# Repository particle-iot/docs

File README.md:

Particle Documentation 
======================

Here you'll find the documentation for the Particle platform, including
the Particle Device Cloud, Photon, Electron, and Spark Core.

To view this documentation, visit [our website](https://docs.particle.io), where the documentation is hosted.

Local Hosting
-------------

This documentation uses a fabulous tool from the folks at Segment called [Metalsmith](http://www.metalsmith.io). Metalsmith is a static site generator that builds static HTML sites from source material in other formats; in this case, Markdown and Handlebars.

To set up a server running at `http://localhost:8080`, follow the installation instructions below...

> _**NOTE:** Any changes made to the source content should be automatically picked up by the browser via `livereload`._

### Bare-metal Hosting

#### Device Setup

To host this documentation locally, you'll need Node.js and npm (see the `engines` section of `package.json` for the exact versions):

If you don't have node.js installed, you can download the installer (LTS recommended) from [nodejs.org](https://nodejs.org/en/).

Once you have Node.js set up, navigate to the `docs` directory on your machine, and use the following commands:

#### Install Dependencies

To install any other necessary dependencies, run:

```none
npm install
```

#### Spell checking

To check the spelling of all Markdown files, run:

```none
npm run spell
```

This is a good idea when you edit any .md files because it not only checks regular spelling, but it will flag if you don't capitalize and spell things exactly like the rest of the docs. For example: U.FL, Wi-Fi, etc..

Actually, these two files are currently skipped because something in the files confuse the spelling checker and cause it to lose track of word breaks and then things fail horribly:

- src/content/reference/asset-tracking/tracker-edge-firmware.md
- src/content/reference/device-os/firmware.md

#### Testing

If you are making non-trivial changes, it’s a good idea to check links using the crawler. This takes a number of minutes to run:

```none
npm test
```

If errors are reported, fix them and run the test again. The second time it will be much faster because it will have cached many of the lookups.

Link checking is not done on commits or pull requests due to the variable amount of time it takes and that it may randomly fail, making it hard to publish at a specific time.

#### Running locally

```none
npm start
```

Once the output stops, 

#### Generate PDF datasheets

```none
npm run pdf-generation
```

### Containerized Hosting

If you have Docker installed, then you can simply run the following commands to get started...

```none
$ cd <particle-iot/docs>/
$ scripts/docker-server.sh --help

usage: particle-docs [--build] [--deploy] [--run-tests] [--spell-check]

Build, test and deploy a local documentation server.

  -b, --build           Build and install documentation packages.
  -d, --deploy          Launch documentation server at https://localhost:8080.
  -h, --help            Display this help and exit.
  -s, --spell-check     Run the spell-checker to verify spelling and update dictionary file.
  -t, --run-tests       Run CI tests.

NOTE: If no options are specified, then ALL options will be selected.
```

> _**NOTE:** Containerized hosting is currently only available on Linux devices. Mac is has an [open issue](https://github.com/docker/for-mac/issues/2965) involving `localhost`, and Windows has not been tested at this time._

The containerized version is not regularly used. It will probably work, but is not guaranteed to.

Command line tools
------------------

The `scripts` directory contains a number of maintenance tools. They all share the dependencies in the top-level `package.json`, so a single `npm install` in the top of the repository is all that's needed. Run them from the top of the repository using `npm run`. To pass options to a tool, put them after `--`:

```none
npm run library-tool -- --generate
```

| Command | Description |
| :--- | :--- |
| `npm run api-rename-section` | Rename a section of the Device OS API reference (interactive) |
| `npm run carriers-update` | Update docs Markdown when `carriers.json` is updated |
| `npm run export-md` | Export a docs page to Markdown (`--dest` is relative to the top of the repository) |
| `npm run fake-data` | Generate fake data (device IDs, serial numbers, ICCIDs) for testing |
| `npm run fix-links` | Fix links within the docs |
| `npm run fix-tracker-hex` | Fix hex files for the Tracker device |
| `npm run library-tool` | Particle library tester and data generating tool (see below) |
| `npm run map-fix` | Update the world map SVG |
| `npm run menu-json-upgrade` | Upgrade menu JSON files |
| `npm run move-page` | Move a docs page and add redirects (interactive) |
| `npm run pin-info-update` | Fix up the `pinInfo.json` file |
| `npm run pinmap-diagram` | Generate pinmap diagram SVG files |
| `npm run power-consumption` | Parse the power consumption reference manual (put the HTML export in `scripts/power-consumption/power.html`) |
| `npm run release-update` | Update release notes and device restore binaries for new Device OS releases |
| `npm run ticket-forms` | Extract ticket forms and fields from the Zendesk guide (requires the `ZENDESK_AUTH` environment variable) |
| `npm run title-case-fixer` | Fix capitalization of Markdown headers |
| `npm run update-app-notes` | Update the application notes tiles from the marketing website (requires Node.js 20 or later) |

The `scripts/ticket-processor` tool runs on a different server, so it is not part of the top-level package. It has its own `package.json` and is run from its own directory using `npm install` and `node app.js`.

### Access token

The `library-tool` and `release-update` tools need a Particle API access token. Copy `scripts/config.example.json` to `scripts/config.json` (which is not committed to git) and edit it:

```json
{
    "accessToken": "xxx"
}
```

Shared code for reading this file is in `scripts/lib/script-config.js`.

### Library tool

```none
npm run library-tool -- --fetch-library-list --download-libraries --test-builds --generate
```

Options:

- `--fetch-library-list` Downloads the library list from the API instead of using `data/libraryList.json`
- `--download-libraries` Downloads any missing libraries to `data/libraries`
- `--test-builds` Tests any libraries that have not been built. Build status is stored in `data/libraryData.json`
- `--generate` Generates data files in the docs repository (this also does `--generate-index`)
- `--generate-index` Generates an abbreviated index of libraries in `src/assets/files/libraryIndex.json`

These are in the `scripts/LibraryTool` directory. Note that `data/libraries` and `data/libraryList.json` are not committed to github, as they are huge and can be regenerated if needed. The build status in `data/libraryData.json` is stored.

Updating Production Documentation
---------------------------------

When updated documentation is pushed to the `master` branch, it is automatically pushed to Amazon S3 by Circle CI.

Organization
------------

The majority of the content herein is stored in the `src/content` directory as a set of Markdown files. Assets such as images and javascript are stored in the `src/assets` directory.

### Structuring your content

The docs dynamically generate a table of contents for navigation purposes based on the headers (i.e. `###`) that you use on each page. It is important to note that _order and hierarchy matters_ when you are designing the organization of content on your page. Your page should include the following:

* 1 `h1` at the top of the page that will serve as the title of the page. You can even copy the `title` directly from the front-matter of the markdown file like this: `# {{title}}`

* As many `h2`s (`##`) as you'd like to serve as the section headers for the page.

* Underneath every `h2`, if applicable, as many `h3`s (`###`) as you'd like to serve as sub-sections within the section. These will appear as nested within the navigation on the left.

Note that there are only 2 levels of navigation that will appear in the table of contents. *`h4`s and below will not appear in the table of contents*.

### Redirects

When moving pages around or defining the default page for a section, add redirect links to [`redirects.json`](config/redirects.json).

Attributions
------------

Some of this documentation is derived from the [Arduino documentation](http://arduino.cc/en/Reference), as the Arduino/Wiring language and libraries are used extensively on the Spark Core.

This documentation was originally built using [Flatdoc](http://ricostacruz.com/flatdoc/), an awesome tool for building beautiful documentation from simple Markdown files. We have made many modifications since, but the inspiration remains.

Contributions
-------------

This documentation is managed by Particle, but supported by the community. We welcome contributions such as:

* Edits to improve grammar or fix typos (run `npm run spell` for automated spell check)
* Edits to improve clarity
* Additional annotated examples for others to follow
* Additional content that would help provide a complete understanding of the Particle platform
* Translations to other languages

Making a contribution is as simple as forking this repository, making edits to your fork, and contributing those edits as a pull request. For more information on how to make a pull request, see [GitHub's documentation](https://help.github.com/articles/using-pull-requests/).

License
-------

These files have been made available online through a [Creative Commons Attribution-ShareAlike 3.0 license](http://creativecommons.org/licenses/by-sa/3.0/us/).

You are welcome to distribute, remix, and use these files for commercial purposes. If you do so, please attribute the original design to Particle both on the website and on the physical packaging of the product or in the instruction manual. All derivative works must be published under the same or a similar license.

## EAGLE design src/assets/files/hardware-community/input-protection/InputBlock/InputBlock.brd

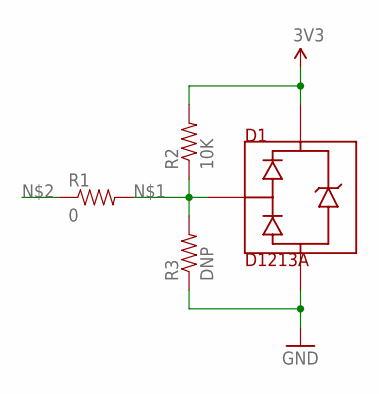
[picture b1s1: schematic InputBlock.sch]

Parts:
D1: D1213A; DLP
R1: 0; 0603-RES
R2: 10K; 0603-RES
R3: DNP; 0603-RES

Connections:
3V3: D1.VCC, R2.2
GND: D1.GND, R3.1
unnamed: D1.SIGNAL, R1.2, R2.1, R3.2

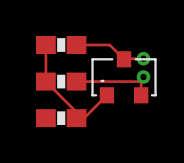
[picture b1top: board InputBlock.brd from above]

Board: 2 copper layers, 4 parts (0 on the bottom side), 3 nets.

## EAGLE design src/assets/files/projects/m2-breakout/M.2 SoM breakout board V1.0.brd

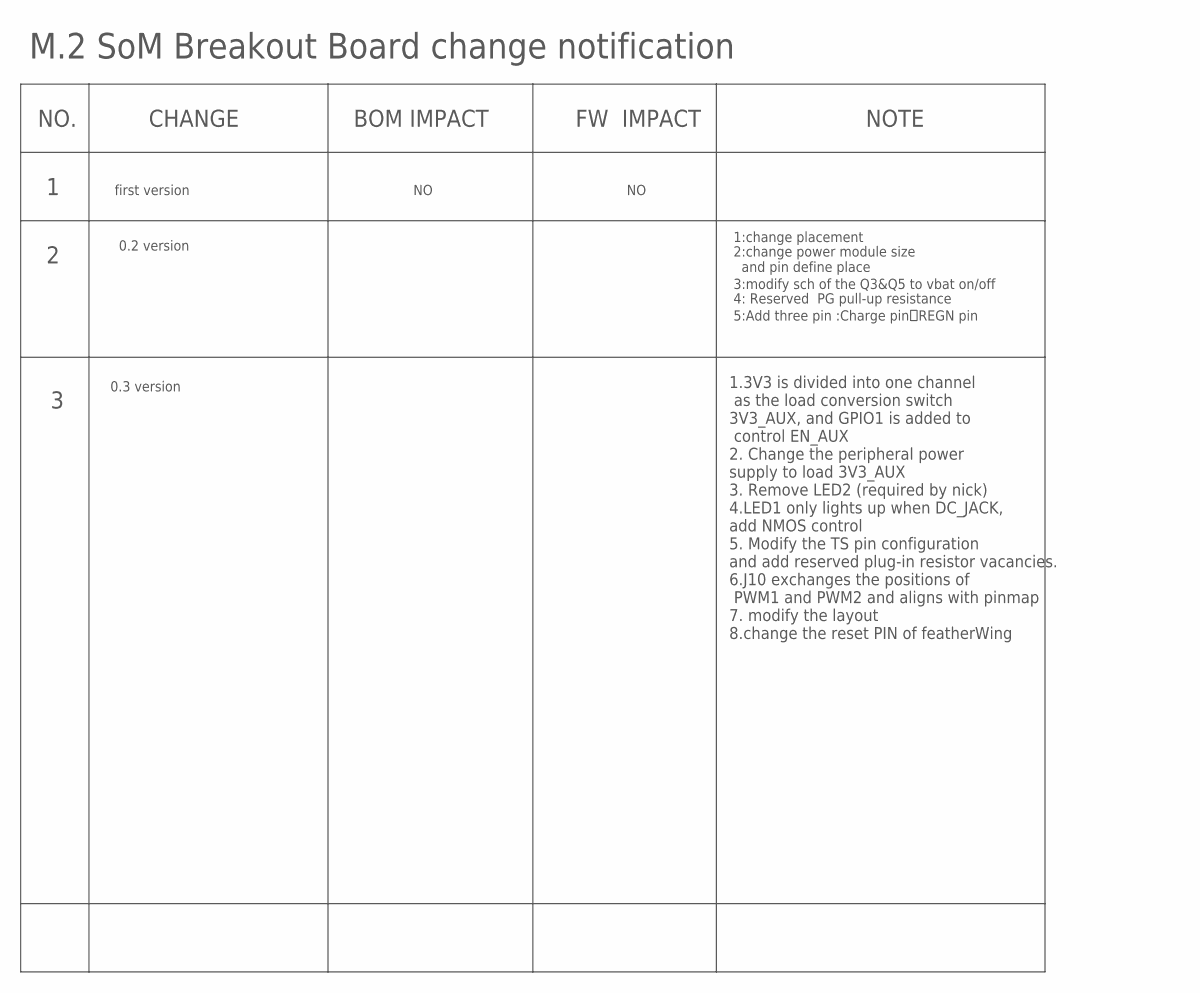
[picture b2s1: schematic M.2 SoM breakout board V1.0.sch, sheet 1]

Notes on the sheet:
NO.
CHANGE
BOM IMPACT
FW IMPACT
NOTE
first version
M.2 SoM Breakout Board change notification
0.2 version
1:change placement
3:modify sch of the Q3&Q5 to vbat on/off
5:Add three pin :Charge pin，REGN pin
2:change power module size and pin define place
4: Reserved PG pull-up resistance
0.3 version
1.3V3 is divided into one channel as the load conversion switch 3V3_AUX, and GPIO1 is added to control EN_AUX 2. Change the peripheral power supply to load 3V3_AUX 3. Remove LED2 (required by nick) 4.LED1 only lights up when DC_JACK, add NMOS control 5. Modify the TS pin configuration and add reser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

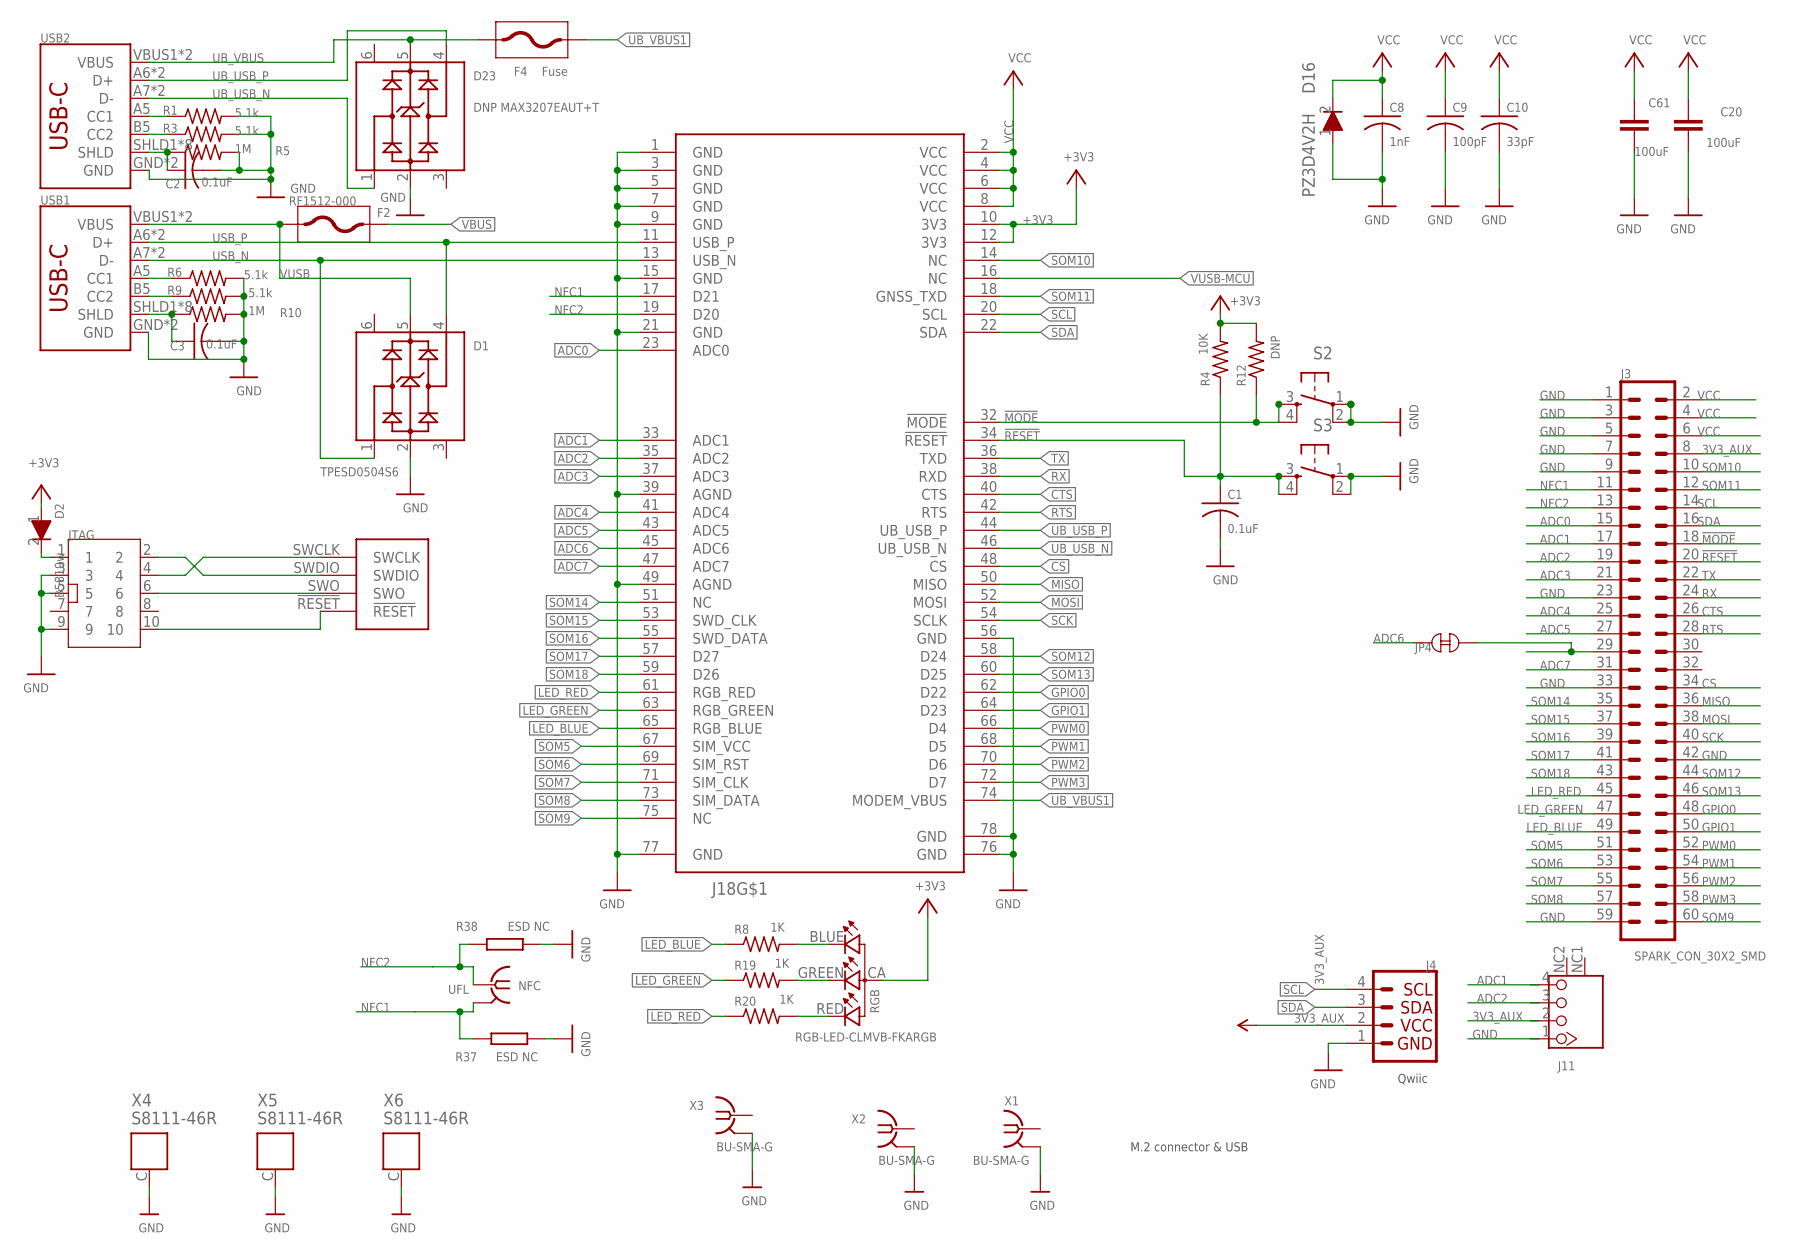
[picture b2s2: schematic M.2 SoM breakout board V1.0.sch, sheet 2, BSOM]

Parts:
C1, C2, C3: 0.1uF; C0402_B
C8: 1nF; C0402_B
C9: 100pF; C0402_B
C10: 33pF; C0402_B
C20, C61: 100uF; C1206K
D1: TPESD0504S6; SOT23-6
D2: B5819w; SOD-123
D16: PZ3D4V2H; SOD-323
D23: DNP MAX3207EAUT+T; SOT23-6
F2: RF1512-000; F0805
F4: Fuse; F0805
J3: SPARK_CON_30X2_SMD
J4: QWIIC_CONNECTORJS-1MM; 1X04_1MM_RA
J11: WAFER-HY2.0-4PWB; M.2-SOM-BREAKOUT-BOARD-V0.2-0228_WAFER-HY2.0-4PWB
J18: PARTICLE-STUDIOS_M_SERIES_M.2KEY; PARTICLE-STUDIOS_PARTICLE_M.2EKEY_3.65MM_DRILL
JP4: TP_SHORT
JTAG: CONN5X2; CONN5X2_1.27; MPN P6014A-M2GC-030-10
NFC: UFL; IPEX-20279-001E
R1, R3, R6, R9: 5.1k; R0402_B
R4: 10K; R0402_B
R5, R10: 1M; R0402_B
R8, R19, R20: 1K; R0402_B
R12: DNP; R0402_B
R37, R38: ESD NC; R-0402S
RGB: RGB-LED-CLMVB-FKARGB; PLCC4-2MM-RGB
S2, S3: TAC_SWITCH; TACTILE_SWITCH_4.2*3.2
USB1, USB2: USB_C16PIN; USB-C-16P
X1, X2, X3: BU-SMA-G
X4, X5, X6: S8111-46R

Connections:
3V3_AUX: J3.8, J4.2, J11.2; also elsewhere on the board
!MODE: J3.18, J18.32 (!MODE), R12.1, S2.3, S2.4
!RESET: C1.1, J3.20, J18.34 (!RESET), J18.!RESET, JTAG.10, R4.1, S3.3, S3.4; also elsewhere on the board
+3V3: D2.1, J18.10 (3V3), J18.12 (3V3), R4.2, R12.2, RGB.CA (1); also elsewhere on the board
ADC0: J3.15, J18.23 (ADC0); also elsewhere on the board
ADC1: J3.17, J11.4, J18.33 (ADC1); also elsewhere on the board
ADC2: J3.19, J11.3, J18.35 (ADC2); also elsewhere on the board
ADC3: J3.21, J18.37 (ADC3); also elsewhere on the board
ADC4: J3.25, J18.41 (ADC4); also elsewhere on the board
ADC5: J3.27, J18.43 (ADC5); also elsewhere on the board
ADC6: J18.45 (ADC6), JP4.2; also elsewhere on the board
ADC7: J3.31, J18.47 (ADC7)
CS: J3.34, J18.48 (CS); also elsewhere on the board
CTS: J3.26, J18.40 (CTS); also elsewhere on the board
GND: C1.2, C2.2, C3.2, C8.2, C9.2, C10.2, C20.2, C61.2, D1.2, D16.1, D23.2, J3.1, J3.3, J3.5, J3.7, J3.9, J3.23, J3.33, J3.42, J3.59, J4.1, J11.1, J18.1 (GND), J18.3 (GND), J18.5 (GND), J18.7 (GND), J18.9 (GND), J18.15 (GND), J18.21 (GND), J18.39 (AGND), J18.49 (AGND), J18.56 (GND), J18.76 (GND), J18.77 (GND), J18.78 (GND), JTAG.3, JTAG.5, JTAG.9, R1.2, R3.2, R5.2, R6.2, R9.2, R10.2, R37.2, R38.1, S2.1, S2.2, S3.1, S3.2, USB1.GND, USB1.GND2 (GND), USB2.GND, USB2.GND2 (GND), X1.2, X1.3 (2), X1.4 (2), X1.5 (2), X2.2, X2.3 (2), X2.4 (2), X2.5 (2), X3.2, X3.3 (2), X3.4 (2), X3.5 (2), X4.C, X5.C, X6.C; also elsewhere on the board
GPIO0: J3.48, J18.62 (D22); also elsewhere on the board
GPIO1: J3.50, J18.64 (D23); also elsewhere on the board
LED_BLUE: J3.49, J18.65 (RGB_BLUE), R8.1
LED_BLUE1: R8.2, RGB.BLUE (2)
LED_GREEN: J3.47, J18.63 (RGB_GREEN), R19.1
LED_GREEN1: R19.2, RGB.GREEN (3)
LED_RED: J3.45, J18.61 (RGB_RED), R20.1
LED_RED1: R20.2, RGB.RED (4)
MISO: J3.36, J18.50 (MISO); also elsewhere on the board
MOSI: J3.38, J18.52 (MOSI); also elsewhere on the board
unnamed: R1.1, USB2.A5 (CC1)
unnamed: R3.1, USB2.B5 (CC2)
unnamed: C2.1, R5.1, USB2.SHLD1 (SHLD), USB2.SHLD2 (SHLD), USB2.SHLD3 (SHLD), USB2.SHLD4 (SHLD), USB2.SHLD5 (SHLD), USB2.SHLD6 (SHLD), USB2.SHLD7 (SHLD), USB2.SHLD8 (SHLD)
unnamed: R6.1, USB1.A5 (CC1)
unnamed: R9.1, USB1.B5 (CC2)
unnamed: D2.2, JTAG.1
unnamed: C3.1, R10.1, USB1.SHLD1 (SHLD), USB1.SHLD2 (SHLD), USB1.SHLD3 (SHLD), USB1.SHLD4 (SHLD), USB1.SHLD5 (SHLD), USB1.SHLD6 (SHLD), USB1.SHLD7 (SHLD), USB1.SHLD8 (SHLD)
unnamed: J3.29, JP4.1
NFC1: J3.11, J18.17 (D21), NFC.2@1 (GND), NFC.2@2 (GND), R37.1
NFC2: J3.13, J18.19 (D20), NFC.1, R38.2
PWM0: J3.52, J18.66 (D4); also elsewhere on the board
PWM1: J3.54, J18.68 (D5); also elsewhere on the board
PWM2: J3.56, J18.70 (D6); also elsewhere on the board
PWM3: J3.58, J18.72 (D7); also elsewhere on the board
RTS: J3.28, J18.42 (RTS)
RX: J3.24, J18.38 (RXD); also elsewhere on the board
SCK: J3.40, J18.54 (SCLK); also elsewhere on the board
SCL: J3.14, J4.4, J18.20 (SCL); also elsewhere on the board
SDA: J3.16, J4.3, J18.22 (SDA); also elsewhere on the board
SOM5: J3.51, J18.67 (SIM_VCC)
SOM6: J3.53, J18.69 (SIM_RST)
SOM7: J3.55, J18.71 (SIM_CLK)
SOM8: J3.57, J18.73 (SIM_DATA)
SOM9: J3.60, J18.75 (NC)
SOM10: J3.10, J18.14 (NC)
SOM11: J3.12, J18.18 (GNSS_TXD)
SOM12: J3.44, J18.58 (D24)
SOM13: J3.46, J18.60 (D25)
SOM14: J3.35, J18.51 (NC)
SOM15: J3.37, J18.53 (SWD_CLK)
SOM16: J3.39, J18.55 (SWD_DATA)
SOM17: J3.41, J18.57 (D27)
SOM18: J3.43, J18.59 (D26)
SWCLK: J18.SWCLK, JTAG.4
SWDIO: J18.SWDIO, JTAG.2
SWO: J18.SWO, JTAG.6
TX: J3.22, J18.36 (TXD); also elsewhere on the board
UB_USB_N: D23.1, J18.46 (UB_USB_N), USB2.A7 (D-), USB2.B7 (D-)
UB_USB_P: D23.4, J18.44 (UB_USB_P), USB2.A6 (D+), USB2.B6 (D+)
UB_VBUS: D23.5, F4.P$2 (2), USB2.VBUS1 (VBUS), USB2.VBUS2 (VBUS)
UB_VBUS1: F4.P$1 (1), J18.74 (MODEM_VBUS)
USB_N: D1.1, J18.13 (USB_N), USB1.A7 (D-), USB1.B7 (D-)
USB_P: D1.4, J18.11 (USB_P), USB1.A6 (D+), USB1.B6 (D+)
VBUS: F2.P$2 (2); also elsewhere on the board
VCC: C8.1, C9.1, C10.1, C20.1, C61.1, D16.2, J3.2, J3.4, J3.6, J18.2 (VCC), J18.4 (VCC), J18.6 (VCC), J18.8 (VCC); also elsewhere on the board
VUSB: D1.5, F2.P$1 (1), USB1.VBUS1 (VBUS), USB1.VBUS2 (VBUS)
VUSB-MCU: J18.16 (NC); also elsewhere on the board

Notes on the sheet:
Qwiic
M.2 connector & USB

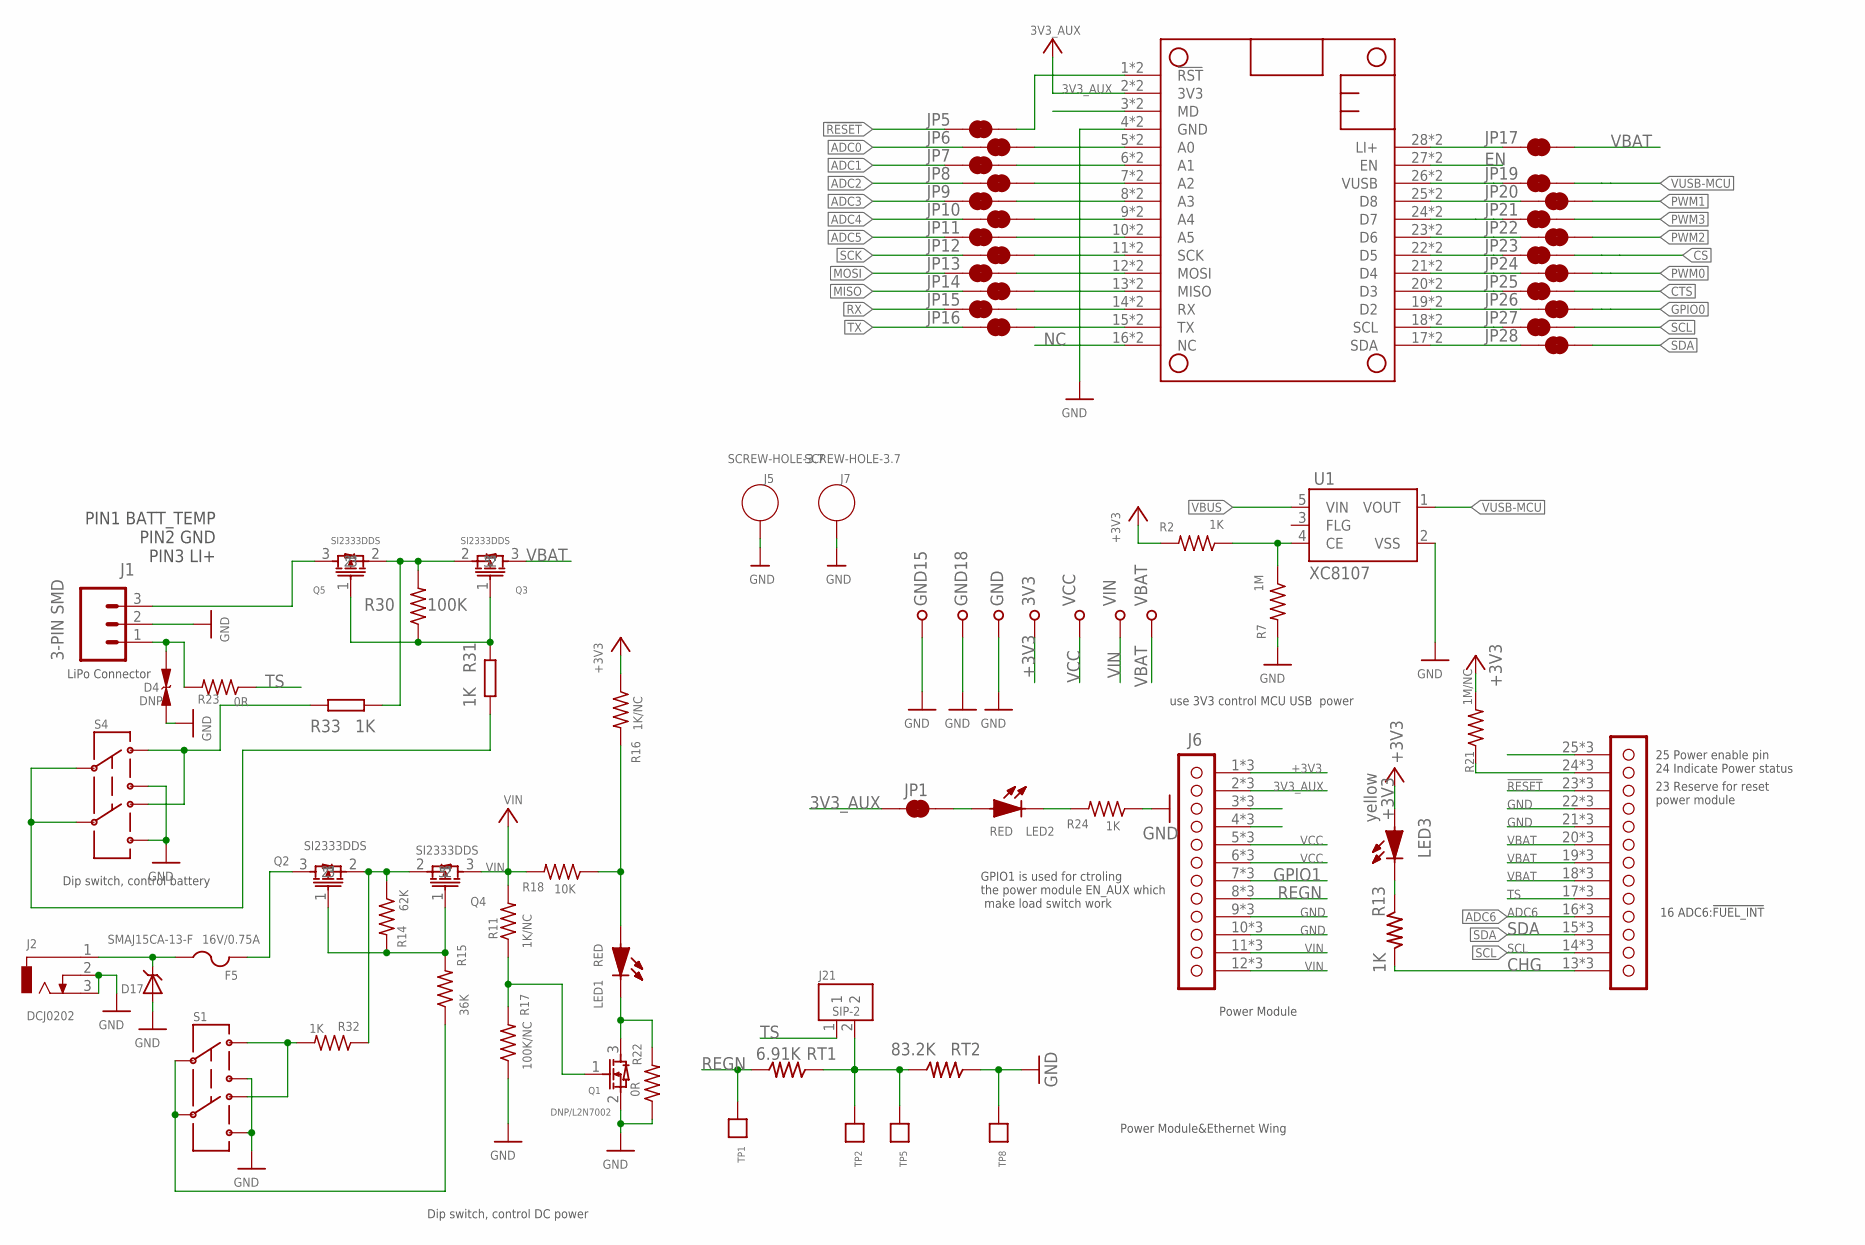
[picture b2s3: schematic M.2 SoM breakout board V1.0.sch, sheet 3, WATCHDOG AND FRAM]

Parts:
3V3: TP-S2751-46R; S2751-46R
D4: DNP; C0402
D17: SMAJ15CA-13-F; SMADIODE
F5: 16V/0.75A; 1812
GND, GND15, GND18: TP-S2751-46R; S2751-46R
J1: 3-PIN SMD; JST-3-SMD
J2: DCJ0202
J5, J7: SCREW-HOLE-3.7
J6: M.2-SOM-BREAKOUT-BOARD-V0.3_M.2-SOM-BREAKOUT-BOAR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; M.2-SOM-BREAKOUT-BOARD-V0.3_M.2-SOM-BREAKOUT-BOARD-V0.2-022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
J21: SIP-2
JP1, JP5, JP6, JP7, JP8, JP9, JP10, JP11, JP12, JP13, JP14, JP15, JP16, JP17, JP19, JP20, JP21, JP22, JP23, JP24, JP25, JP26, JP27, JP28: JUMPER-SMT_2_NC_TRACE_NO-SILK; SMT-JUMPER_2_NC_TRACE_NO-SILK
LED1, LED2: RED; LED0603
LED3: yellow; LED0603
MS1: PARTICLE_MESH_SMTDUAL; FEATHERWING_SMT2
Q1: DNP/L2N7002; SOT323
Q2, Q3, Q4, Q5: SI2333DDS; SOT-23
R2, R24, R32: 1K; R0402_B
R7: 1M; R0402_B
R11, R16: 1K/NC; R0402_B
R13, R31, R33: 1K; R-0402S
R14: 62K; R0402_B
R15: 36K; R0402_B
R17: 100K/NC; R0402_B
R18: 10K; R0402_B
R21: 1M/NC; R0402_B
R22, R23: 0R; R0402_B
R30: 100K; R0603_P
RT1: 6.91K; R-0603A
RT2: 83.2K; R-0603A
S1, S4: SWITCH-DPDT; SWITCH-2.5X3.2-6
TP1, TP2, TP5, TP8: TPTPEB; TPEB
U1: XC8107; SOT25
VBAT: TP-S2751-46R; S2751-46R
VCC: TP-S2751-46R; S2751-46R
VIN: TP-S2751-46R; S2751-46R

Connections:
3V3_AUX: J6.2 (3V3), J6.@2 (3V3), J6.P$2 (3V3), JP1.1, MS1.2 (3V3), MS1.2' (3V3); also elsewhere on the board
!RESET: J6.23 (!RST), J6.@23 (!RST), J6.P$23 (!RST), JP5.1; also elsewhere on the board
+3V3: 3V3.1, J6.1 (3V3), J6.@1 (3V3), J6.P$1 (3V3), LED3.1 (A), R2.2, R16.1, R21.2; also elsewhere on the board
ADC0: JP6.1; also elsewhere on the board
ADC1: JP7.1; also elsewhere on the board
ADC2: JP8.1; also elsewhere on the board
ADC3: JP9.1; also elsewhere on the board
ADC4: JP10.1; also elsewhere on the board
ADC5: JP11.1; also elsewhere on the board
ADC6: J6.16 (!FUEL-INT), J6.@16 (!FUEL-INT), J6.P$16 (!FUEL-INT); also elsewhere on the board
CHG: J6.13 (CHG), J6.@13 (CHG), J6.P$13 (CHG), R13.2
CS: JP23.2; also elsewhere on the board
CTS: JP25.2; also elsewhere on the board
EN: MS1.27 (EN), MS1.27' (EN)
GND: D4.1, D17.A, GND.1, GND15.1, GND18.1, J1.2, J2.2, J2.3, J5.P$1, J6.9 (GND), J6.10 (GND), J6.21 (GND), J6.22 (GND), J6.@9 (GND), J6.@10 (GND), J6.@21 (GND), J6.@22 (GND), J6.P$9 (GND), J6.P$10 (GND), J6.P$21 (GND), J6.P$22 (GND), J7.P$1, MS1.4 (GND), MS1.4' (GND), Q1.2, R7.2, R17.1, R22.1, R24.1, RT2.1, S1.3, S1.6, S4.3, S4.6, TP8.1, U1.2 (VSS); also elsewhere on the board
GPIO0: JP26.2; also elsewhere on the board
GPIO1: J6.7 (REGN), J6.@7 (REGN), J6.P$7 (REGN); also elsewhere on the board
LI+: JP17.1, MS1.28 (LI+), MS1.28' (LI+)
MISO: JP14.1; also elsewhere on the board
MOSI: JP13.1; also elsewhere on the board
unnamed: MS1.3 (MD), MS1.3' (MD)
unnamed: R2.1, R7.1, U1.4 (CE)
unnamed: Q2.2, Q4.2, R14.1, R32.1
unnamed: F5.2, Q2.3
unnamed: LED3.2 (K), R13.1
unnamed: J21.2, RT1.1, RT2.2, TP2.1, TP5.1
unnamed: LED2.2 (K), R24.2
unnamed: JP21.1, MS1.24 (D7), MS1.24' (D7)
unnamed: Q2.1, Q4.1, R14.2, R15.2
unnamed: LED1.1 (A), R16.2, R18.1
unnamed: Q1.1, R11.1, R17.2
unnamed: R33.1, S4.1, S4.4
unnamed: JP6.2, MS1.5 (A0), MS1.5' (A0)
unnamed: J6.24 (PG), J6.@24 (PG), J6.P$24 (PG), R21.1
unnamed: JP7.2, MS1.6 (A1), MS1.6' (A1)
unnamed: JP8.2, MS1.7 (A2), MS1.7' (A2)
unnamed: JP9.2, MS1.8 (A3), MS1.8' (A3)
unnamed: JP10.2, MS1.9 (A4), MS1.9' (A4)
unnamed: JP11.2, MS1.10 (A5), MS1.10' (A5)
unnamed: JP12.2, MS1.11 (SCK), MS1.11' (SCK)
unnamed: JP13.2, MS1.12 (MOSI), MS1.12' (MOSI)
unnamed: JP14.2, MS1.13 (MISO), MS1.13' (MISO)
unnamed: JP15.2, MS1.14 (RX), MS1.14' (RX)
unnamed: JP16.2, MS1.15 (TX), MS1.15' (TX)
unnamed: R32.2, S1.1, S1.4
unnamed: JP28.1, MS1.17 (SDA), MS1.17' (SDA)
unnamed: JP27.1, MS1.18 (SCL), MS1.18' (SCL)
unnamed: LED1.2 (K), Q1.3, R22.2
unnamed: JP26.1, MS1.19 (D2), MS1.19' (D2)
unnamed: JP25.1, MS1.20 (D3), MS1.20' (D3)
unnamed: JP24.1, MS1.21 (D4), MS1.21' (D4)
unnamed: JP23.1, MS1.22 (D5), MS1.22' (D5)
unnamed: JP22.1, MS1.23 (D6), MS1.23' (D6)
unnamed: JP20.1, MS1.25 (D8), MS1.25' (D8)
unnamed: J6.3 (5DC), J6.@3 (5DC), J6.P$3 (5DC)
unnamed: D17.C, F5.1, J2.1
unnamed: JP5.2, MS1.1 (!RST), MS1.1' (!RST)
unnamed: JP1.2, LED2.1 (A)
unnamed: J6.25 (ENABLE), J6.@25 (ENABLE), J6.P$25 (ENABLE)
unnamed: R15.1, S1.2, S1.5
unnamed: J1.3, Q5.3
unnamed: J6.4 (5DC), J6.@4 (5DC), J6.P$4 (5DC)
unnamed: D4.2, J1.1, R23.2
unnamed: Q3.2, Q5.2, R30.2, R33.2
unnamed: Q3.1, Q5.1, R30.1, R31.1
unnamed: R31.2, S4.2, S4.5
NC: MS1.16 (NC), MS1.16' (NC)
PWM0: JP24.2; also elsewhere on the board
PWM1: JP20.2; also elsewhere on the board
PWM2: JP22.2; also elsewhere on the board
PWM3: JP21.2; also elsewhere on the board
REGN: J6.8 (NC), J6.@8 (NC), J6.P$8 (NC), RT1.2, TP1.1
RX: JP15.1; also elsewhere on the board
SCK: JP12.1; also elsewhere on the board
SCL: J6.14 (SCL), J6.@14 (SCL), J6.P$14 (SCL), JP27.2; also elsewhere on the board
SDA: J6.15 (SDA), J6.@15 (SDA), J6.P$15 (SDA), JP28.2; also elsewhere on the board
TS: J6.17 (TS), J6.@17 (TS), J6.P$17 (TS), J21.1, R23.1
TX: JP16.1; also elsewhere on the board
V-USB: JP19.1, MS1.26 (VUSB), MS1.26' (VUSB)
VBAT: J6.18 (VBAT), J6.19 (VBAT), J6.20 (VBAT), J6.@18 (VBAT), J6.@19 (VBAT), J6.@20 (VBAT), J6.P$18 (VBAT), J6.P$19 (VBAT), J6.P$20 (VBAT), JP17.2, Q3.3, VBAT.1
VBUS: U1.5 (VIN); also elsewhere on the board
VCC: J6.5 (VCC), J6.6 (VCC), J6.@5 (VCC), J6.@6 (VCC), J6.P$5 (VCC), J6.P$6 (VCC), VCC.1; also elsewhere on the board
VIN: J6.11 (VIN), J6.12 (VIN), J6.@11 (VIN), J6.@12 (VIN), J6.P$11 (VIN), J6.P$12 (VIN), Q4.3, R11.2, R18.2, VIN.1
VUSB-MCU: JP19.2, U1.1 (VOUT); also elsewhere on the board

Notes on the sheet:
LiPo Connector
16 ADC6:!FUEL_INT
Power Module
Dip switch, control battery
Dip switch, control DC power
use 3V3 control MCU USB power
Power Module&Ethernet Wing
PIN1 BATT_TEMP PIN2 GND PIN3 LI+
24 Indicate Power status
25 Power enable pin
23 Reserve for reset power module
GPIO1 is used for ctroling the power module EN_AUX which make load switch work

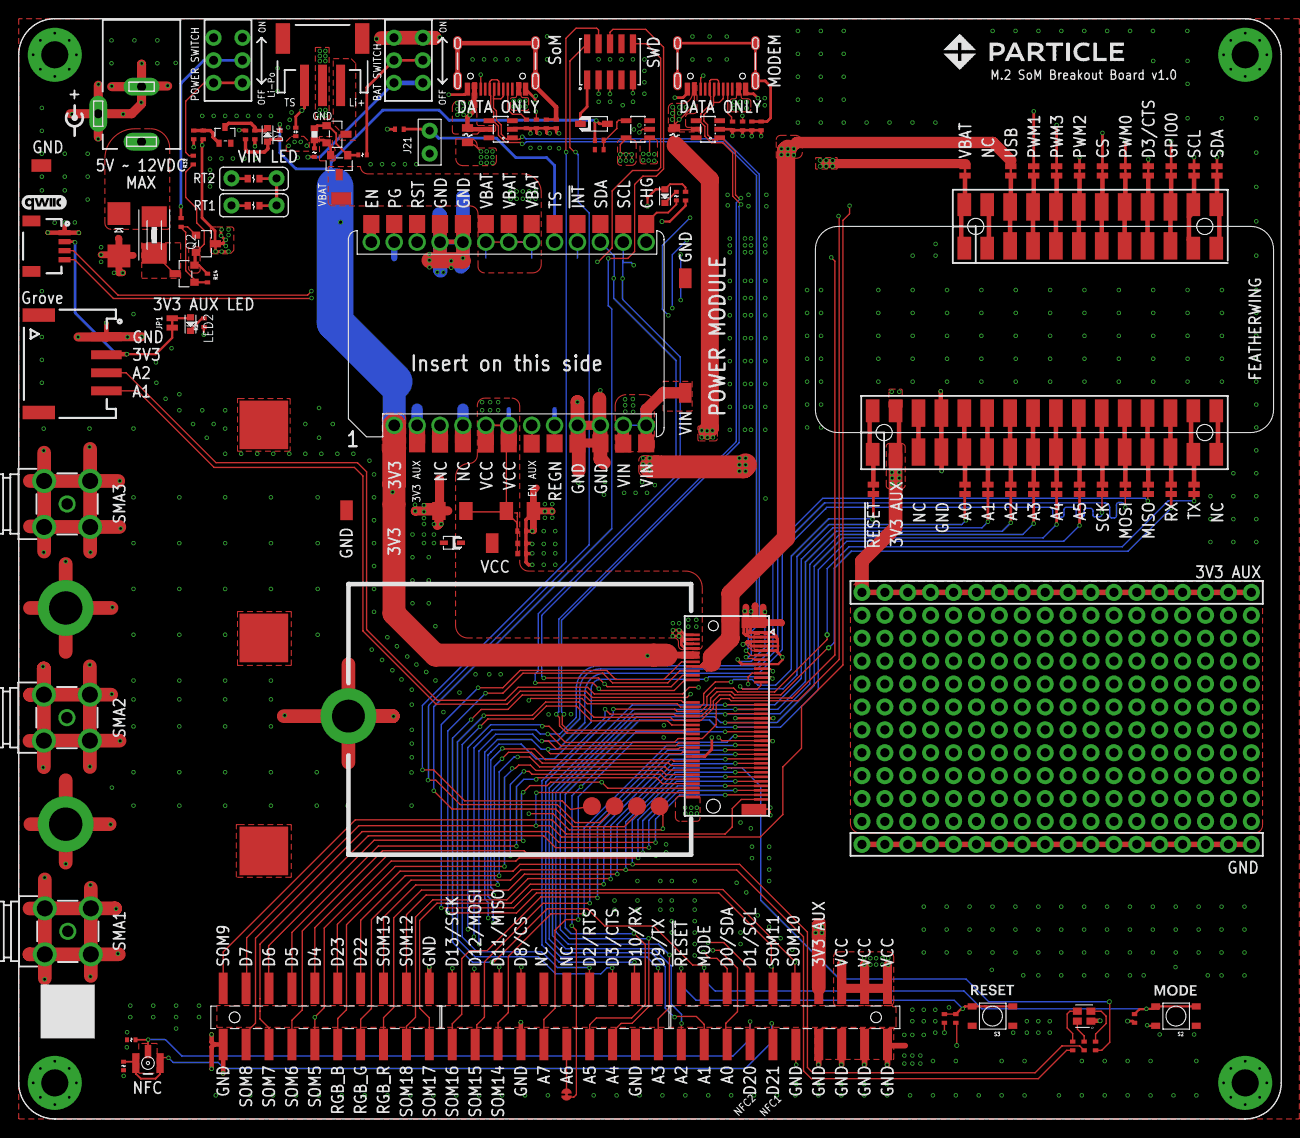
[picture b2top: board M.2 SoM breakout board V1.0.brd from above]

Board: 4 copper layers, 140.0 x 122.0 mm, 121 parts (0 on the bottom side), 127 nets.

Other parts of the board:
LOGO2: QWIIC_LOGO_5MM; QWIIC_5MM

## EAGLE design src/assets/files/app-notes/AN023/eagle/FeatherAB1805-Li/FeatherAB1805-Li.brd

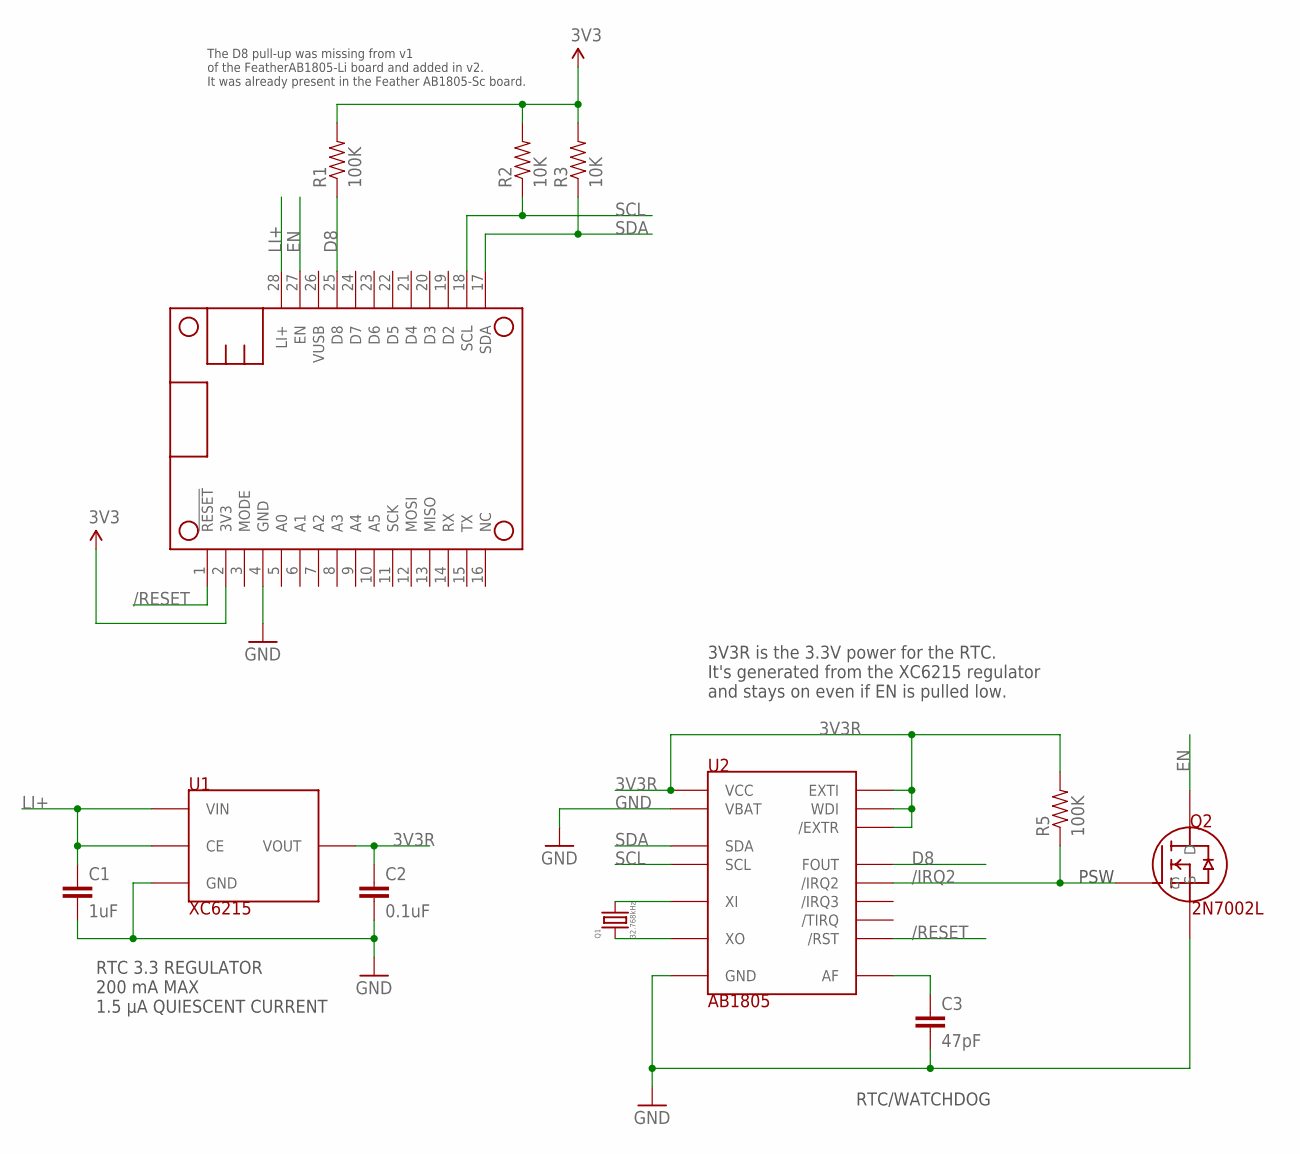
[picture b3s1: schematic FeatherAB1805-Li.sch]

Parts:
C1: 1uF; 0603-CAP
C2: 0.1uF; 0603-CAP
C3: 47pF; 0603-CAP
MS1: FEATHERWING_NODIM
Q1: 32.768kHz; ABS07-120-CRYSTAL
Q2: 2N7002L
R1, R5: 100K; 0603-RES
R2, R3: 10K; 0603-RES
U1: XC6215; SOT-25-TOREX
U2: AB1805; 16-VFQFN-ABRACON

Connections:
3V3: MS1.2 (3V3), R1.2, R2.2, R3.2
3V3R: C2.1, R5.2, U1.5 (VOUT), U2.2 (WDI), U2.3 (/EXTR), U2.10 (EXTI), U2.13 (VCC)
/IRQ2: Q2.1 (G), R5.1, U2.4 (/IRQ2)
/RESET: MS1.1 (!RESET), U2.1 (/RST)
AF: C3.1, U2.14 (AF)
D8: MS1.25 (D8), R1.1, U2.11 (FOUT)
EN: MS1.27 (EN), Q2.3 (D)
GND: C1.2, C2.2, C3.2, MS1.4 (GND), Q2.2 (S), U1.2 (GND), U2.5 (VBAT), U2.9 (GND), U2.EP (GND)
LI+: C1.1, MS1.28 (LI+), U1.1 (VIN), U1.3 (CE)
SCL: MS1.18 (SCL), R2.1, U2.7 (SCL)
SDA: MS1.17 (SDA), R3.1, U2.6 (SDA)
XI: Q1.2, U2.16 (XI)
XO: Q1.1, U2.15 (XO)

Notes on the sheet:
RTC 3.3 REGULATOR 200 mA MAX 1.5 µA QUIESCENT CURRENT
PSW
RTC/WATCHDOG
3V3R is the 3.3V power for the RTC. It's generated from the XC6215 regulator and stays on even if EN is pulled low.
The D8 pull-up was missing from v1 of the FeatherAB1805-Li board and added in v2. It was already present in the Feather AB1805-Sc board.

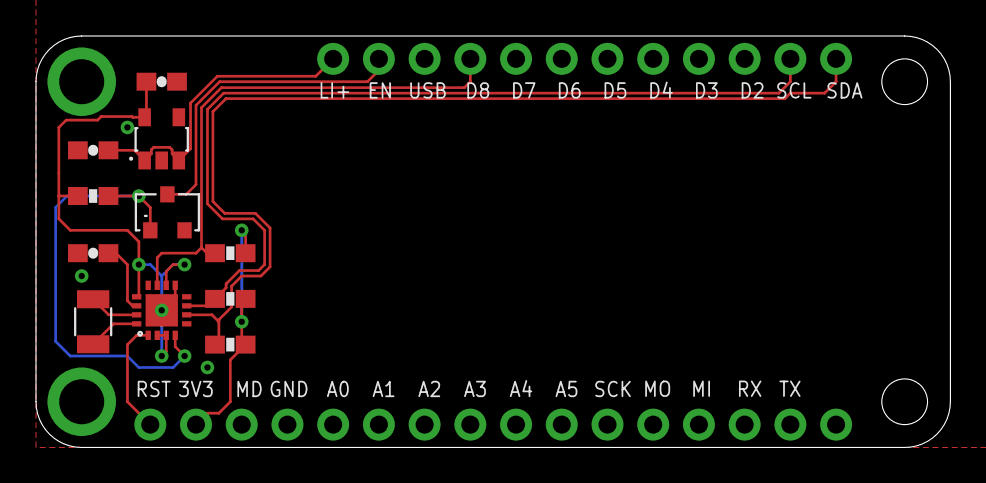
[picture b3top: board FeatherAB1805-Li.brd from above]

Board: 2 copper layers, 50.8 x 22.9 mm, 12 parts (0 on the bottom side), 13 nets.

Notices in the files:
parts and their libraries:
SparkFun-Retired: Licensing: Creative Commons ShareAlike 4.0 International - https://creativecommons.org/licenses/by-sa/4.0
con-headers-jp: Copyright (C) 2008, Bob Starr
